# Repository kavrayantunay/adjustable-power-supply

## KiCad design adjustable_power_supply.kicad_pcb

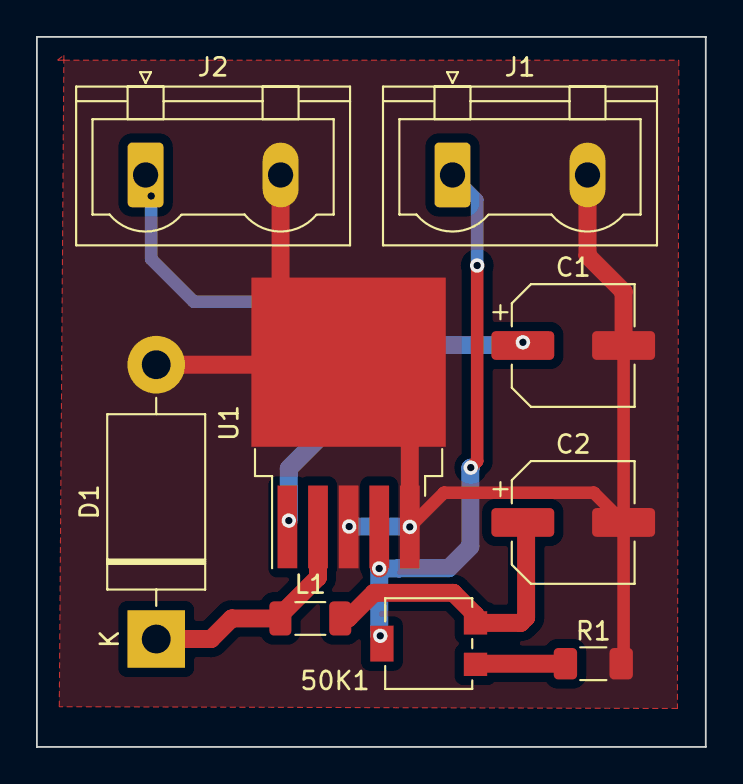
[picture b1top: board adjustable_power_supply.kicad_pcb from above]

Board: 2 copper layers, 37.2 x 39.4 mm, 9 parts (0 on the bottom side), 6 nets.

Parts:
50K1: R_Potentiometer; Potentiometer_Bourns_3224G_Horizontal
C1, C2: C_Polarized; CP_Elec_6.3x5.9
D1: 1N5822; D_DO-201AD_P15.24mm_Horizontal
J1, J2: klemens; PhoenixContact_GMSTBVA_2,5_2-G_1x02_P7.50mm_Vertical
L1: 150uH; L_1206_3216Metric_Pad1.22x1.90mm_HandSolder
R1: 1.21K; R_1206_3216Metric_Pad1.30x1.75mm_HandSolder
U1: LM2576HVS-ADJ; TO-263-5_TabPin3

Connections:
GND: C1.2, C2.2, D1.2 (A), J1.2 (GND), J2.2 (GND), R1.2, U1.3 (GND), U1.5 (~ON/OFF)
unnamed: 50K1.1, C2.1, L1.2
unnamed: 50K1.2, J1.1 (Vcc), U1.4 (FB)
unnamed: 50K1.3, R1.1
unnamed: D1.1 (K), L1.1, U1.2 (OUT)
unnamed: C1.1, J2.1 (Vcc), U1.1 (VIN)
